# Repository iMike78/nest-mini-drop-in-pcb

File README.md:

<div align="right">
  <details>
    <summary >🌐 Language</summary>
    <div>
      <div align="center">
        <a href="https://openaitx.github.io/view.html?user=iMike78&project=nest-mini-drop-in-pcb&lang=en">English</a>
        | <a href="https://openaitx.github.io/view.html?user=iMike78&project=nest-mini-drop-in-pcb&lang=zh-CN">简体中文</a>
        | <a href="https://openaitx.github.io/view.html?user=iMike78&project=nest-mini-drop-in-pcb&lang=zh-TW">繁體中文</a>
        | <a href="https://openaitx.github.io/view.html?user=iMike78&project=nest-mini-drop-in-pcb&lang=ja">日本語</a>
        | <a href="https://openaitx.github.io/view.html?user=iMike78&project=nest-mini-drop-in-pcb&lang=ko">한국어</a>
        | <a href="https://openaitx.github.io/view.html?user=iMike78&project=nest-mini-drop-in-pcb&lang=hi">हिन्दी</a>
        | <a href="https://openaitx.github.io/view.html?user=iMike78&project=nest-mini-drop-in-pcb&lang=th">ไทย</a>
        | <a href="https://openaitx.github.io/view.html?user=iMike78&project=nest-mini-drop-in-pcb&lang=fr">Français</a>
        | <a href="https://openaitx.github.io/view.html?user=iMike78&project=nest-mini-drop-in-pcb&lang=de">Deutsch</a>
        | <a href="https://openaitx.github.io/view.html?user=iMike78&project=nest-mini-drop-in-pcb&lang=es">Español</a>
        | <a href="https://openaitx.github.io/view.html?user=iMike78&project=nest-mini-drop-in-pcb&lang=it">Italiano</a>
        | <a href="https://openaitx.github.io/view.html?user=iMike78&project=nest-mini-drop-in-pcb&lang=ru">Русский</a>
        | <a href="https://openaitx.github.io/view.html?user=iMike78&project=nest-mini-drop-in-pcb&lang=pt">Português</a>
        | <a href="https://openaitx.github.io/view.html?user=iMike78&project=nest-mini-drop-in-pcb&lang=nl">Nederlands</a>
        | <a href="https://openaitx.github.io/view.html?user=iMike78&project=nest-mini-drop-in-pcb&lang=pl">Polski</a>
        | <a href="https://openaitx.github.io/view.html?user=iMike78&project=nest-mini-drop-in-pcb&lang=ar">العربية</a>
        | <a href="https://openaitx.github.io/view.html?user=iMike78&project=nest-mini-drop-in-pcb&lang=fa">فارسی</a>
        | <a href="https://openaitx.github.io/view.html?user=iMike78&project=nest-mini-drop-in-pcb&lang=tr">Türkçe</a>
        | <a href="https://openaitx.github.io/view.html?user=iMike78&project=nest-mini-drop-in-pcb&lang=vi">Tiếng Việt</a>
        | <a href="https://openaitx.github.io/view.html?user=iMike78&project=nest-mini-drop-in-pcb&lang=id">Bahasa Indonesia</a>
        | <a href="https://openaitx.github.io/view.html?user=iMike78&project=nest-mini-drop-in-pcb&lang=as">অসমীয়া</
      </div>
    </div>
  </details>

</div>

# MiciMike drop-in PCB replacement for Google Nest Mini

[MiciMike Nest Mini](https://github.com/iMike78/nest-mini-drop-in-pcb) is an open-source drop-in PCB replacement for the ["Google Nest Mini" (Google's second-generation smart speaker with a barrel connector charging port)](https://en.wikipedia.org/wiki/Google_Nest_(smart_speakers)). It is built around the ESP32-S3, ESP32-P4 and (optionally) ESP32-C6 and is meant to run open-source firmware, primarily [ESPHome](https://esphome.io).

Tip! If you are instead looking for a similar drop-in PCB replacement for the "Google Home Mini" (Google's first-generation smart speaker with a Micro-USB charging port), check out the sister project at https://github.com/iMike78/home-mini-v1-drop-in-pcb

Both are fully open-source hardware projects. They take concept inspiration from the [Onju Voice](https://github.com/justLV/onju-voice) and from the [Home Assistant Voice Preview Edition](https://www.home-assistant.io/blog/2024/12/19/voice-preview-edition-the-era-of-open-voice/) by the Open Home Foundation and Nabu Casa.

# Project scope

The goal of this project is a custom replacement PCB for the Google Nest Mini (2nd Gen) that fits the original enclosure and reuses the original speaker, power supply, flex cable, mute switch and touch surface.

It primarily targets people who want to convert their old Google Nest Mini into an open-source [voice satellite for Home Assistant](https://www.home-assistant.io/voice_control/) and/or a media-player speaker for [Music Assistant](https://www.music-assistant.io). Because it is based on the Espressif ESP32 platform, the hardware can be used with other firmware as well.

### Relation to the Home Assistant Voice Preview Edition

Earlier revisions of this board followed the Voice Preview Edition (Voice PE) reference design closely, including its XMOS XU316 audio processor. The goal is still the same kind of device: a local, open voice assistant for Home Assistant running ESPHome, with on-device wake word detection and a cleaned-up microphone signal.

The hardware has since moved away from the Voice PE. Microcontroller technology has evolved beyond the XMOS-based approach, and this revision uses an ESP32-P4 for audio processing instead. The P4 may not outperform the XMOS in every respect, but it is a more open platform: it is programmed with Espressif's open-source ESP-IDF, the same ecosystem as the ESP32-S3 and ESPHome, instead of a separate proprietary toolchain. As a result, this board is **not hardware-compatible** with the Voice PE, and the Voice PE firmware does not run on it unchanged.

Developing new ESPHome features is out of scope for this repository. The Voice PE firmware remains a useful reference, and general features belong upstream in ESPHome:

- https://github.com/esphome/home-assistant-voice-pe
  - https://github.com/esphome/esphome
      - https://github.com/esphome/feature-requests

## Current status

> [!CAUTION]
> The rev 3 schematic and PCB are complete and pass ERC/DRC, but the design has **not yet been validated on hardware**. A prototype run is the next step. Do not order production quantities from these files yet.

- Schematic and layout are complete (KiCad 10), with schematic/PCB parity and no unconnected items.
- The final BOM / MPN review is still in progress.
- Mechanical fit of the 5.1 mm tall amplifier output inductors (L11/L12) must be checked on the prototype.
- The ESPHome configuration in this repository (`MiciMike.yaml`) targets an earlier hardware revision and **does not match** the current board.
- ESP32-P4 audio firmware (microphone processing) is under development.

## Hardware variants

One PCB, two assembly variants. They are defined as KiCad 10 design variants, so the BOM, position file and fabrication outputs can be generated per variant.

| Variant | Description | Radios |
|---|---|---|
| **Full** | ESP32-S3 + ESP32-P4 + ESP32-C6 | Wi-Fi 4 / BLE (S3), Wi-Fi 6 / BLE / 802.15.4 Thread & Zigbee (C6) |
| **No C6** | ESP32-S3 + ESP32-P4, the whole ESP32-C6 section not populated | Wi-Fi 4 / BLE (S3) |

In the **No C6** variant all 27 parts of the ESP32-C6 sheet are DNP (U8, Y2, AE2, its RF matching network, decoupling, FB2 and the C6 boot/reset parts). FB2 is the only feed of the C6 supply rail, so the whole C6 power domain is unpowered. The S3 GPIOs that connect to the C6 (reset, GPIO9/boot, UART) must not be used by the firmware in this variant.

Example exports with `kicad-cli`:

```
kicad-cli sch export bom --variant "No C6" -o bom_noC6.csv nest-mini-v2-drop-in-pcb.kicad_sch
kicad-cli pcb export pos --variant "No C6" --exclude-dnp -o pos_noC6.csv nest-mini-v2-drop-in-pcb.kicad_pcb
```

## Architecture

| Block | Part | Role |
|---|---|---|
| Main MCU | ESP32-S3R8 (8 MB PSRAM) + 16 MB W25Q128 flash | Wi-Fi/BLE, ESPHome, wake word, I²S master to the amplifier, I²C master, LEDs, mute detection, boot/reset and UART control of the P4 and C6 |
| Audio processor | ESP32-P4 + 16 MB W25Q128 flash | Microphone input and audio processing (noise suppression, AEC, AGC; firmware in development) |
| Thread / Zigbee (optional) | ESP32-C6FH8 (8 MB in-package flash) | 802.15.4 radio, e.g. OpenThread Border Router (ESP-IDF `ot_br`) |
| Amplifier | TAS5805M (TAS5805MPWPR) | Class-D amplifier with DSP, I²S audio, I²C control by the S3 |
| Microphones | 3x TDK InvenSense T3902 (MMICT390200012) | PDM MEMS microphones to the ESP32-P4 |
| Touch | MPR121 | Capacitive touch on the original touch surface, I²C with IRQ to the S3 |
| LEDs | 4x SK6805-EC20 + 2x SK6812D-EC3210R (side-emitting, board edge) | Addressable RGB, driven by the S3 through an SN74AHCT1G125 3.3 V to 5 V level shifter |

The ESP32-P4 replaces the XMOS XU316 used in earlier revisions.

### Inter-chip links

- **S3 → amplifier:** I²S (BCLK, LRCK, SDIN) and I²C control.
- **Amplifier → P4 (AEC reference):** the TAS5805M SDOUT goes to the ESP32-P4, which receives BCLK/LRCK from the same I²S bus, so the P4 gets the post-DSP playback signal as the echo-cancellation reference.
- **S3 ↔ P4:** I²S data line from the P4 to the S3 (I2S_DIN_SEC, processed microphone audio) and a second I²S clock pair (I2S2 BCLK/LRCLK), plus UART, P4_BOOT and P4_RST driven by the S3.
- **S3 ↔ C6:** UART plus C6 reset and GPIO9 (boot), driven by the S3, for firmware updates of the C6 from the S3.
- **I²C bus:** S3, TAS5805M and MPR121.

## Power

- **Input:** 14 V from the original Nest Mini power supply (14 V / 1.1 A), through the original flex cable (Hirose FH34SRJ-10S, 14 V on pins 7–10).
- **Protection:** PMEG4030ER Schottky diode in series (reverse polarity) and SMAJ15A TVS on the 14 V rail.
- **Rails:**
  - 14 V → TPS62130 → 5 V (LEDs, microphone LDO, LED level shifter)
  - 5 V → TPS62130 → 3.3 V, then separate filtered branches through ferrite beads for the S3, P4 and C6
  - 3.3 V → TLV62569 → ESP32-P4 core supply (ESP_VDD_HP)
  - 14 V → TAS5805M PVDD
  - 5 V → TLV73333 → microphone supply (switched off by the mute switch)
- **Bench supply / test pads:**

| Pad | Rail | Type | Powers |
|---|---|---|---|
| TP1 (+) / TP4 (GND) | +14 V, **max 15 V** | 3 mm THT pads (front) | the whole board, including the amplifier |
| TP2 | +5 V | 1 mm test pad (back) | everything except the amplifier (TAS5805M PVDD stays off) |
| TP3 | +3.3 V | 1 mm test pad (back) | the ESP32s, flash, touch controller; no LEDs, no microphones, no amplifier |

Use only one supply input at a time. When feeding +5 V or +3.3 V directly, the rail above it is not driven, and the regulator in front of it may be back-powered through its internal switch.

> ⚠️ There is no USB-C port on this revision. The board is powered through the original flex cable or the bench / test pads above.

## Audio

- TAS5805M in **mono PBTL** mode with pre-filter paralleling (OUT_A+ ∥ OUT_A− → L11 and OUT_B+ ∥ OUT_B− → L12, per TI TAS5805M PBTL wiring), output filter with 2x Coilcraft XAL5050-103 (10 µH) inductors.
- Original 4 Ω / 15 W speaker. The original firmware limits the amplifier to about 40 %. The firmware must set PBTL mode (`DAMP_PBTL`) and a gain / power limit that suits the speaker and the 14 V / 1.1 A supply.
- Speaker connection: TE 1775443-2 connector (J5) or the parallel solder pads TP8/TP9.

## Microphones and mute

- 3 PDM microphones, connected to the ESP32-P4 through an SN74LVC125A buffer.
- The original mute slide switch (flex cable pin 2) is read by the S3 and also acts **in hardware**: in the muted position the microphone LDO is switched off and the buffer outputs go high-impedance, so the microphones cannot be enabled from firmware.

## Programming

Each ESP has its own unpopulated 5-pin pogo / header footprint: GND, BOOT, RST, USB D−, USB D+.

| Header | Chip | USB |
|---|---|---|
| J1 | ESP32-S3 | native USB (USB Serial/JTAG) |
| J2 | ESP32-C6 | native USB (USB Serial/JTAG) |
| J3 | ESP32-P4 | USB 1.1 FS (GPIO24/25) |

After the first flash, the S3 can update the P4 and the C6 over UART, controlling their boot and reset lines.

## PCB

- 4 layers, 1.6 mm: F.Cu signal / In1 solid GND / In2 power planes / B.Cu signal.
- All vias 0.4 / 0.3 mm (24 thermal vias under the TAS5805M).
- Two Johanson 2450AT18A100E chip antennas (S3 and C6), each with its own keepout, LC matching network, RF netclass and GND via fence.
- GND stitching vias along the board edge.
- Custom DRC rules (`.kicad_dru`) allow the narrow RF track at the ESP32-S3 and ESP32-C6 antenna pins.
- Intentional DRC exclusions (microphone pads at the acoustic openings, touch pads with NPTH, I²S fan-out, programming footprint overlap) are documented with reasons in the project file.

## Hardware changes compared to rev 2

- XMOS XU316 replaced by ESP32-P4 (with its own flash and TLV62569 core supply).
- ESP32-C6 section added as an assembly option (Full / No C6 variants).
- USB-C input, FUSB302B PD controller, USB mux and the GPIO expander removed. Power comes from the original 14 V input, or from the 14 V / 5 V / 3.3 V bench and test pads.
- Programming moved to per-chip pogo footprints with USB.
- S3 controls the P4 and C6 boot/reset lines and has a UART to both.
- 14 V input protection added (series Schottky + TVS), plus bench supply pads TP1/TP4 (14 V) and test pads TP2 (5 V) / TP3 (3.3 V).
- Speaker solder pads TP8/TP9 added next to the speaker connector.
- TAS5805M changed to mono PBTL with 10 µH / XAL5050 output inductors.
- Microphone buffer and microphone LDO controlled by the hardware mute switch.
- TPS62130 regulators: DEF tied to GND, PG not used.
- Complete re-layout in KiCad 10, with RF keepouts, matching networks and via fencing for both antennas.

## Tools used

- 🛠️ KiCad 10
- 🧰 SnapEDA / LCSC for footprint sourcing

## References

### Home Assistant Voice Preview Edition resources (inspiration)
- https://www.home-assistant.io/blog/2024/12/19/voice-preview-edition-the-era-of-open-voice/
  - https://voice-pe.home-assistant.io/resources/
    - https://support.nabucasa.com/hc/en-us/articles/26195279589277-Home-Assistant-Voice-Preview-Edition-PCB-design-files
      - https://raw.githubusercontent.com/NabuCasa/support/refs/heads/main/static/docs/voice/home_assistant_voice_pe_schematic_v1.0_241009.pdf

#### ESPHome firmware for Home Assistant Voice PE

- https://github.com/esphome/home-assistant-voice-pe
  - https://esphome.github.io/home-assistant-voice-pe/
- https://voice-pe.home-assistant.io/

### ESP32-P4 resources

- https://www.espressif.com/en/products/socs/esp32-p4
- https://documentation.espressif.com/esp32-p4_datasheet_en.html
- https://docs.espressif.com/projects/esp-idf/en/latest/esp32p4/

## License

This project is licensed under the [CERN Open Hardware License Version 2 - Strongly Reciprocal (CERN-OHL-S v2)](LICENCE).
Any modified version of this hardware must also be distributed under the same license.

## Development note

AI agents were used as assistants during the development of this hardware, for design review, verification and documentation. All design decisions and the final design files are the author's own.

☕ If you'd like to support this project, feel free to [buy me a coffee on Ko-fi](https://ko-fi.com/imike78)!

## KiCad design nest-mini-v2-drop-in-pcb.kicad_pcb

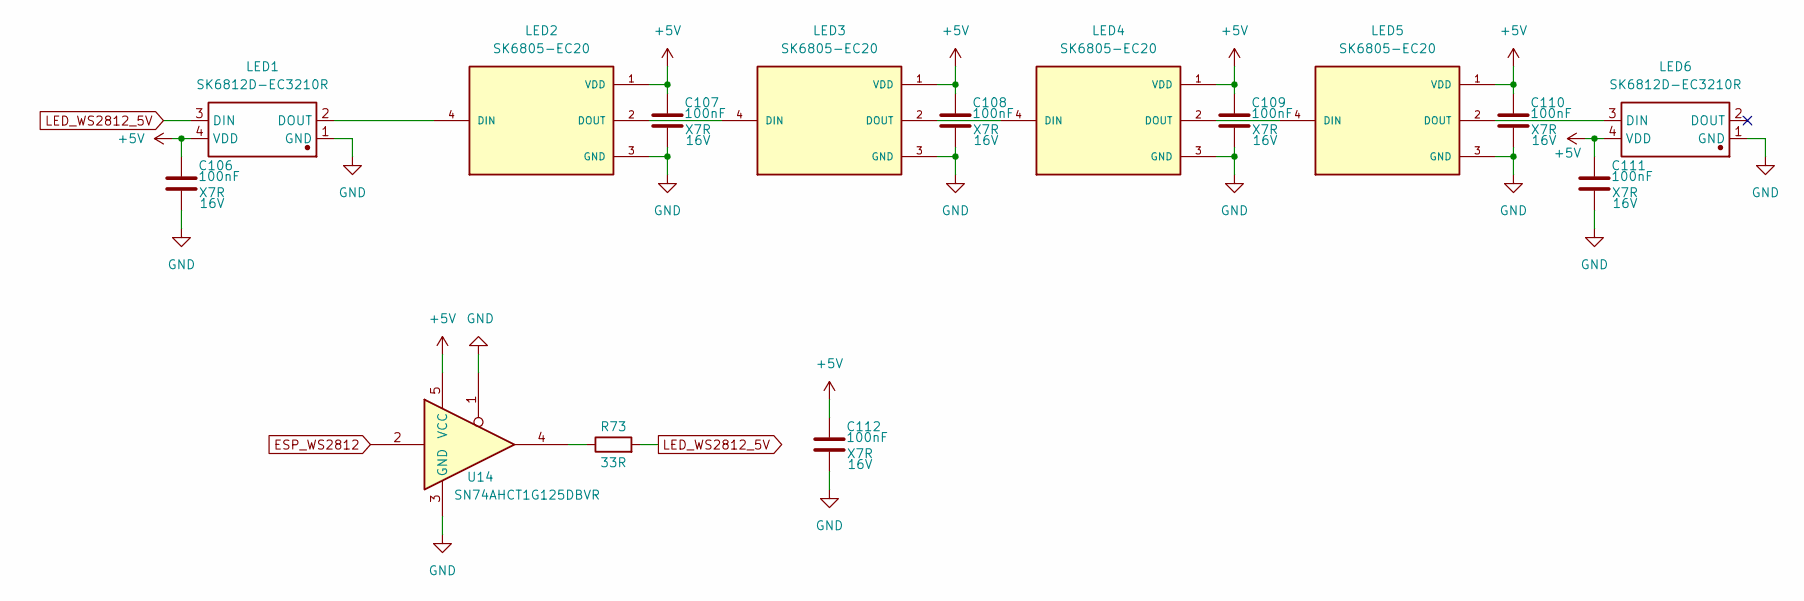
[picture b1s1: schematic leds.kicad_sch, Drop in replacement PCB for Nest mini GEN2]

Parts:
C106, C107, C108, C109, C110, C111, C112: 100nF; C_0402_1005Metric; Voltage 16V; Manufacturer Part CL05B104KO5NNNC; LCSC Part # C1525
LED1, LED6: SK6812D-EC3210R; LED-SMD_4P_SK6812D-EC3210R; Manufacturer Part SK6812D-EC3210R; LCSC Part # C2890041
LED2, LED3, LED4, LED5: SK6805-EC20; Manufacturer Part SK6805-EC20; LCSC Part # C2890036
R73: 33R; R_0402_1005Metric; Tolerance 1%; Manufacturer Part 0402WGF330JTCE; LCSC Part # C25105
U14: SN74AHCT1G125DBVR; SOT-23-5; Manufacturer Part SN74AHCT1G125DBVR; LCSC Part # C7484

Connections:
+5V: C106.1, C107.1, C108.1, C109.1, C110.1, C111.1, C112.1, LED1.4 (VDD), LED2.1 (VDD), LED3.1 (VDD), LED4.1 (VDD), LED5.1 (VDD), LED6.4 (VDD), U14.5 (VCC); also elsewhere on the board
ESP_WS2812: U14.2; also elsewhere on the board
GND: C106.2, C107.2, C108.2, C109.2, C110.2, C111.2, C112.2, LED1.1 (GND), LED2.3 (GND), LED3.3 (GND), LED4.3 (GND), LED5.3 (GND), LED6.1 (GND), U14.1, U14.3 (GND); also elsewhere on the board
LED_WS2812_5V: LED1.3 (DIN), R73.2
unnamed: LED1.2 (DOUT), LED2.4 (DIN)
unnamed: LED2.2 (DOUT), LED3.4 (DIN)
unnamed: LED3.2 (DOUT), LED4.4 (DIN)
unnamed: LED4.2 (DOUT), LED5.4 (DIN)
unnamed: LED5.2 (DOUT), LED6.3 (DIN)
unnamed: R73.1, U14.4

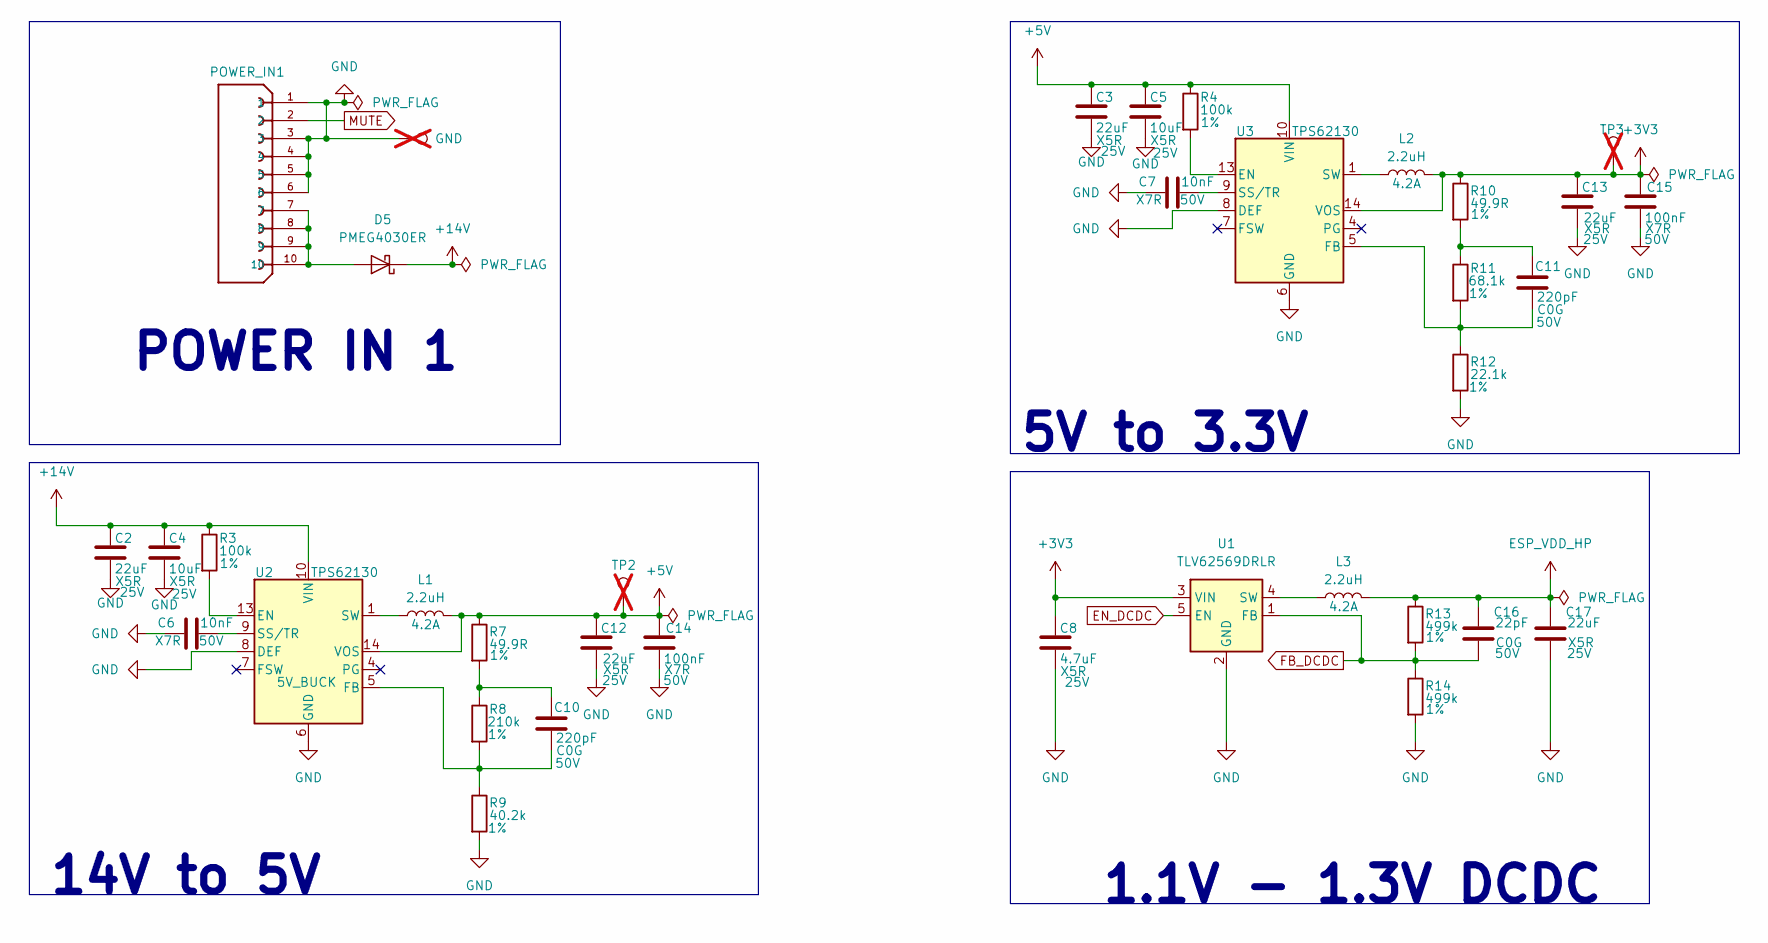
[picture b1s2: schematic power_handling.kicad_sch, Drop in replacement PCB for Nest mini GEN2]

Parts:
C2, C3, C12, C13, C17: 22uF; C_0805_2012Metric; Voltage 25V; Manufacturer Part CL21A226MAQNNNE; LCSC Part # C45783
C4, C5: 10uF; C_0805_2012Metric; Voltage 25V; Manufacturer Part CL21A106KAYNNNE; LCSC Part # C15850
C6, C7: 10nF; C_0402_1005Metric; Voltage 50V; Manufacturer Part CL05B103KB5NNNC; LCSC Part # C15195
C8: 4.7uF; C_0805_2012Metric; Voltage 25V; Manufacturer Part CL21A475KAQNNNE; LCSC Part # C1779
C10, C11: 220pF; C_0603_1608Metric; Voltage 50V; Manufacturer Part 0603CG221J500NT; LCSC Part # C156398
C14, C15: 100nF; C_0805_2012Metric; Voltage 50V; Manufacturer Part CC0805KRX7R9BB104; LCSC Part # C49678
C16: 22pF; C_0402_1005Metric; Voltage 50V; Manufacturer Part 0402CG220J500NT; LCSC Part # C1555
D5: PMEG4030ER; Nexperia_CFP3_SOD-123W; Manufacturer Part PMEG4030ER,115; LCSC Part # C389355
L1, L2, L3: 2.2uH; IND_SRP4020TA-2R2M; Manufacturer Part SRP4020TA-2R2M; LCSC Part # C719179
POWER_IN1: FH34SRJ-10S-0.5SH_50_; HRS_FH34SRJ-10S-0.5SH_50_; Manufacturer Part FH34SRJ-10S-0.5SH(50); LCSC Part # C324723
R3, R4: 100k; R_0402_1005Metric; Tolerance 1%; Manufacturer Part 0402WGF1003TCE; LCSC Part # C25741
R7, R10: 49.9R; R_0603_1608Metric; Tolerance 1%; Manufacturer Part 0603WAF499JT5E; LCSC Part # C23185
R8: 210k; R_0603_1608Metric; Tolerance 1%; Manufacturer Part 0603WAF2103T5E; LCSC Part # C22952
R9: 40.2k; R_0603_1608Metric; Tolerance 1%; Manufacturer Part 0603WAF4022T5E; LCSC Part # C12447
R11: 68.1k; R_0603_1608Metric; Tolerance 1%; Manufacturer Part 0603WAF6812T5E; LCSC Part # C25976
R12: 22.1k; R_0603_1608Metric; Tolerance 1%; Manufacturer Part 0603WAF2212T5E; LCSC Part # C25961
R13, R14: 499k; R_0603_1608Metric; Tolerance 1%; Manufacturer Part ARG03DTC4993; LCSC Part # C2828669
TP2: +5V; TestPoint_Pad_D1.0mm; not fitted
TP3: +3V3; TestPoint_Pad_D1.0mm; not fitted
TP4: GND; TestPoint_THTPad_D3.0mm_Drill1.5mm; not fitted
U1: TLV62569DRLR; SOT-563; Manufacturer Part TLV62569DRLR
U2, U3: TPS62130; VQFN-16-1EP_3x3mm_P0.5mm_EP1.68x1.68mm_ThermalVias; Manufacturer Part TPS62130ARGTR; LCSC Part # C337502

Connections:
+3V3: C8.1, C13.1, C15.1, L2.2, R10.1, TP3.1 (1_1), U1.3 (VIN), U3.14 (VOS); also elsewhere on the board
+5V: C3.1, C5.1, C12.1, C14.1, L1.2, R4.1, R7.1, TP2.1 (1_1), U2.14 (VOS), U3.10 (VIN), U3.11 (VIN), U3.12 (VIN); also elsewhere on the board
+14V: C2.1, C4.1, D5.1 (K), R3.1, U2.10 (VIN), U2.11 (VIN), U2.12 (VIN); also elsewhere on the board
EN_DCDC: U1.5 (EN); also elsewhere on the board
ESP_VDD_HP: C16.1, C17.1, L3.2, R13.1; also elsewhere on the board
FB_DCDC: C16.2, R13.2, R14.1, U1.1 (FB); also elsewhere on the board
GND: C2.2, C3.2, C4.2, C5.2, C6.1, C7.1, C8.2, C12.2, C13.2, C14.2, C15.2, C17.2, POWER_IN1.1, POWER_IN1.3, POWER_IN1.4, POWER_IN1.5, POWER_IN1.6, R9.2, R12.2, R14.2, TP4.1 (1_1), U1.2 (GND), U2.6 (GND), U2.8 (DEF), U2.15 (GND), U2.16 (GND), U2.17 (GND), U3.6 (GND), U3.8 (DEF), U3.15 (GND), U3.16 (GND), U3.17 (GND); also elsewhere on the board
MUTE: POWER_IN1.2; also elsewhere on the board
unnamed: C10.1, R7.2, R8.1
unnamed: C11.1, R10.2, R11.1
unnamed: D5.2 (A), POWER_IN1.7, POWER_IN1.8, POWER_IN1.9, POWER_IN1.10
unnamed: L1.1, U2.1 (SW), U2.2 (SW), U2.3 (SW)
unnamed: L2.1, U3.1 (SW), U3.2 (SW), U3.3 (SW)
unnamed: L3.1, U1.4 (SW)
unnamed: R3.2, U2.13 (EN)
unnamed: C10.2, R8.2, R9.1, U2.5 (FB)
unnamed: C6.2, U2.9 (SS/TR)
unnamed: R4.2, U3.13 (EN)
unnamed: C11.2, R11.2, R12.1, U3.5 (FB)
unnamed: C7.2, U3.9 (SS/TR)

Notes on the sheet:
POWER IN 1
14V to 5V
1.1V - 1.3V DCDC
5V to 3.3V

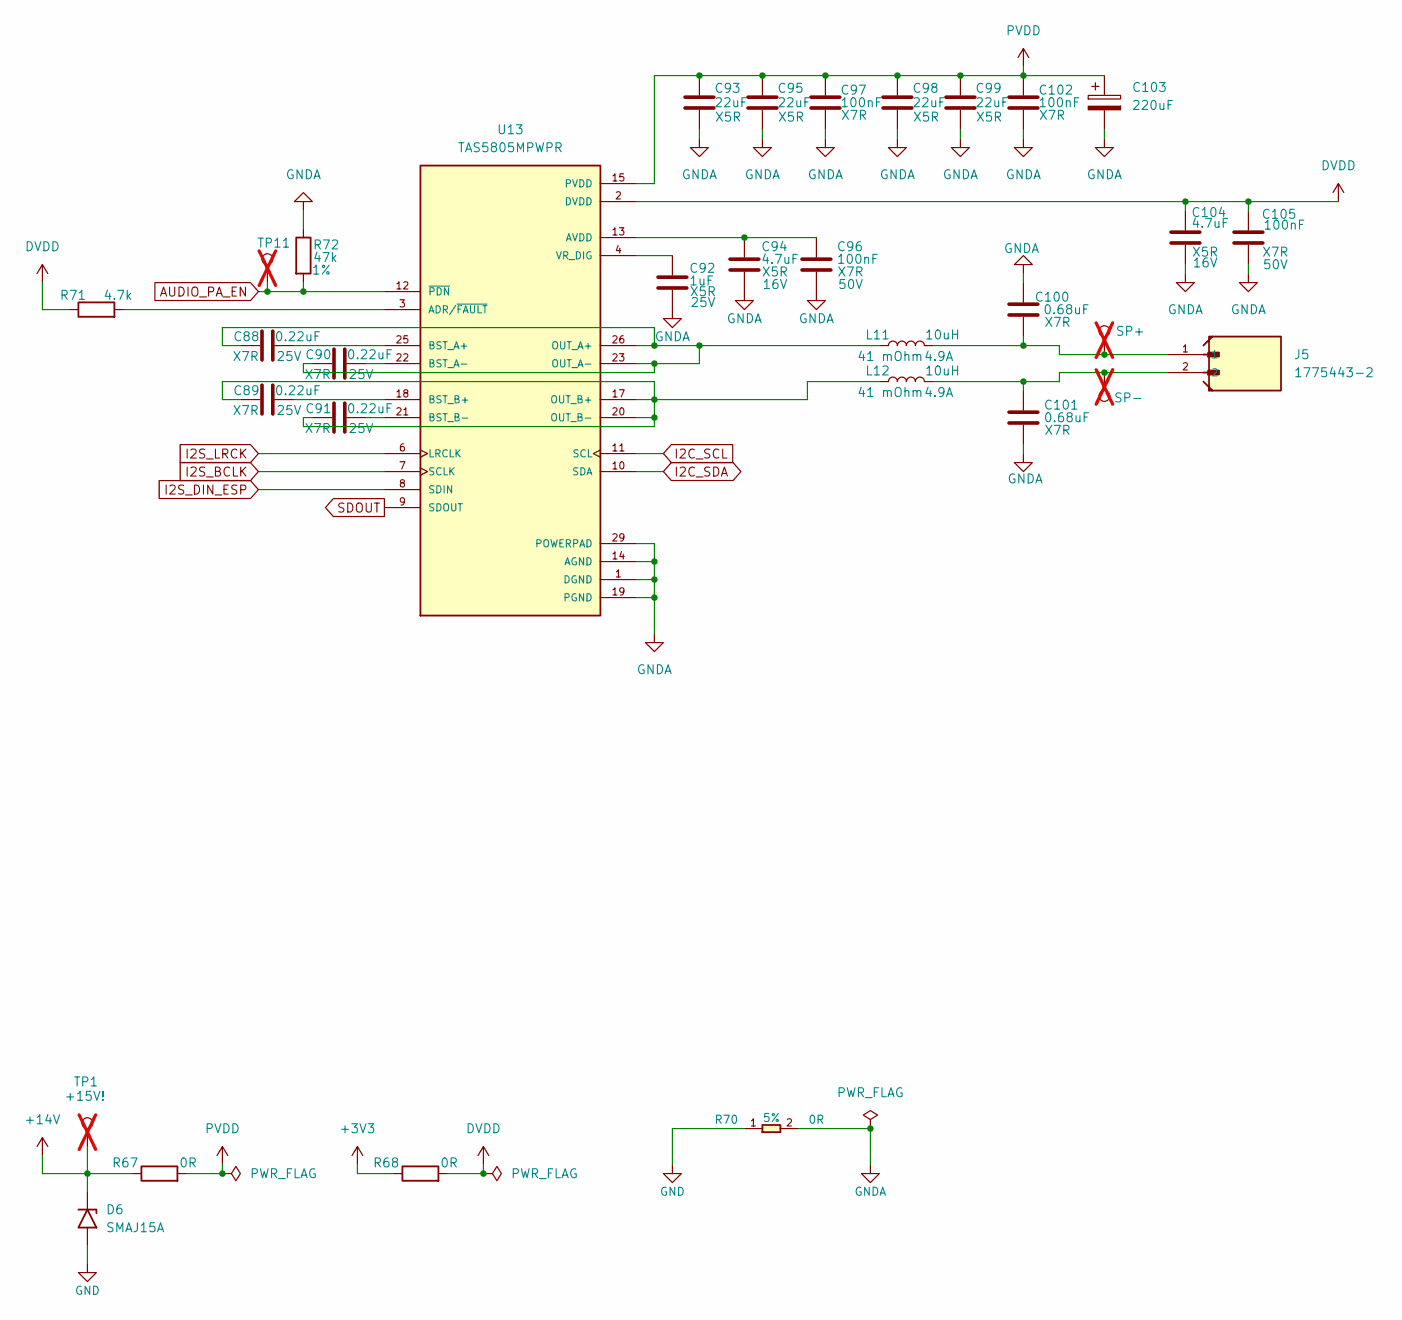
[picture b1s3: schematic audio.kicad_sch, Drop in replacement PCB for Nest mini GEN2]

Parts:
C88, C89, C90, C91: 0.22uF; C_0603_1608Metric; Voltage 25V; Manufacturer Part CL10B224KA8NNNC; LCSC Part # C21120
C92: 1uF; C_0402_1005Metric; Voltage 25V; Manufacturer Part CL05A105KA5NQNC; LCSC Part # C52923
C93, C95, C98, C99: 22uF; C_0805_2012Metric; Voltage 25V; Manufacturer Part CL21A226MAQNNNE; LCSC Part # C45783
C94, C104: 4.7uF; C_0603_1608Metric; Voltage 16V; Manufacturer Part CL10A475KO8NNNC; LCSC Part # C19666
C96, C105: 100nF; C_0603_1608Metric; Voltage 50V; Manufacturer Part CC0603KRX7R9BB104; LCSC Part # C14663
C97, C102: 100nF; C_0402_1005Metric; Voltage 50V; Manufacturer Part CC0402KRX7R9BB104; LCSC Part # C131394
C100, C101: 0.68uF; C_0805_2012Metric; Voltage 50V; Manufacturer Part CL21B684KBFVPNE; LCSC Part # C472832
C103: 220uF; C_Elec_6.3x7.7; Voltage 25V; Manufacturer Part MA25V220M6X8; LCSC Part # C46550464
D6: SMAJ15A; D_SMA; Manufacturer Part SMAJ15A; LCSC Part # C148216
J5: 1775443-2; PARTREV B5; LCSC Part # C5162845
L11, L12: 10uH; L_Coilcraft_XAL5050-XXX; Manufacturer Part XAL5050-103MEC; LCSC Part # C5441578
R67: 0R; R_1206_3216Metric; Manufacturer Part 1206W4F0000T5E; LCSC Part # C17888
R68: 0R; R_0603_1608Metric; Manufacturer Part 0603WAF0000T5E; LCSC Part # C21189
R70: 0R; R_0805_2012Metric; Tolerance 5%; MPN 0805W8F0000T5E; LCSC Part # C17477
R71: 4.7k; R_0402_1005Metric; Manufacturer Part 0402WGF4701TCE; LCSC Part # C25900
R72: 47k; R_0402_1005Metric; Tolerance 1%; Manufacturer Part 0402WGF4702TCE; LCSC Part # C25792
TP1: +15V!; TestPoint_THTPad_D3.0mm_Drill1.5mm; not fitted
TP8: SP+; TestPoint_Pad_D2.0mm; not fitted
TP9: SP-; TestPoint_Pad_D2.0mm; not fitted
TP11: PA_EN; TestPoint_Pad_D1.0mm; not fitted
U13: TAS5805MPWPR; Manufacturer Part TAS5805MPWPR; LCSC Part # C478472

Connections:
+3V3: R68.1; also elsewhere on the board
+14V: D6.1 (A1), R67.1, TP1.1 (1_1); also elsewhere on the board
AUDIO_PA_EN: R72.2, TP11.1 (1_1), U13.12 (~PDN); also elsewhere on the board
DVDD: C104.1, C105.1, R68.2, R71.1, U13.2 (DVDD)
GND: D6.2 (A2), R70.1; also elsewhere on the board
GNDA: C92.2, C93.2, C94.2, C95.2, C96.2, C97.2, C98.2, C99.2, C100.2, C101.2, C102.2, C103.2, C104.2, C105.2, R70.2, R72.1, U13.1 (DGND), U13.5 (DGND), U13.14 (AGND), U13.19 (PGND), U13.24 (PGND), U13.29 (POWERPAD), U13.30 (POWERPAD), U13.31 (POWERPAD), U13.32 (POWERPAD), U13.33 (POWERPAD), U13.34 (POWERPAD), U13.35 (POWERPAD), U13.36 (POWERPAD), U13.37 (POWERPAD), U13.38 (POWERPAD), U13.39 (POWERPAD), U13.40 (POWERPAD), U13.41 (POWERPAD), U13.42 (POWERPAD), U13.43 (POWERPAD), U13.44 (POWERPAD), U13.45 (POWERPAD), U13.46 (POWERPAD), U13.47 (POWERPAD), U13.48 (POWERPAD), U13.49 (POWERPAD), U13.50 (POWERPAD), U13.51 (POWERPAD), U13.52 (POWERPAD), U13.53 (POWERPAD)
I2C_SCL: U13.11 (SCL); also elsewhere on the board
I2C_SDA: U13.10 (SDA); also elsewhere on the board
I2S_BCLK: U13.7 (SCLK); also elsewhere on the board
I2S_DIN_ESP: U13.8 (SDIN); also elsewhere on the board
I2S_LRCK: U13.6 (LRCLK); also elsewhere on the board
unnamed: C100.1, J5.1, L11.2, TP8.1 (1_1)
unnamed: C101.1, J5.2, L12.2, TP9.1 (1_1)
unnamed: R71.2, U13.3 (ADR/~FAULT)
unnamed: C94.1, C96.1, U13.13 (AVDD)
unnamed: C88.2, U13.25 (BST_A+)
unnamed: C90.2, U13.22 (BST_A-)
unnamed: C89.2, U13.18 (BST_B+)
unnamed: C91.2, U13.21 (BST_B-)
unnamed: C88.1, C90.1, L11.1, U13.23 (OUT_A-), U13.26 (OUT_A+)
unnamed: C89.1, C91.1, L12.1, U13.17 (OUT_B+), U13.20 (OUT_B-)
unnamed: C92.1, U13.4 (VR_DIG)
PVDD: C93.1, C95.1, C97.1, C98.1, C99.1, C102.1, C103.1, R67.2, U13.15 (PVDD), U13.16 (PVDD), U13.27 (PVDD), U13.28 (PVDD)
SDOUT: U13.9 (SDOUT); also elsewhere on the board

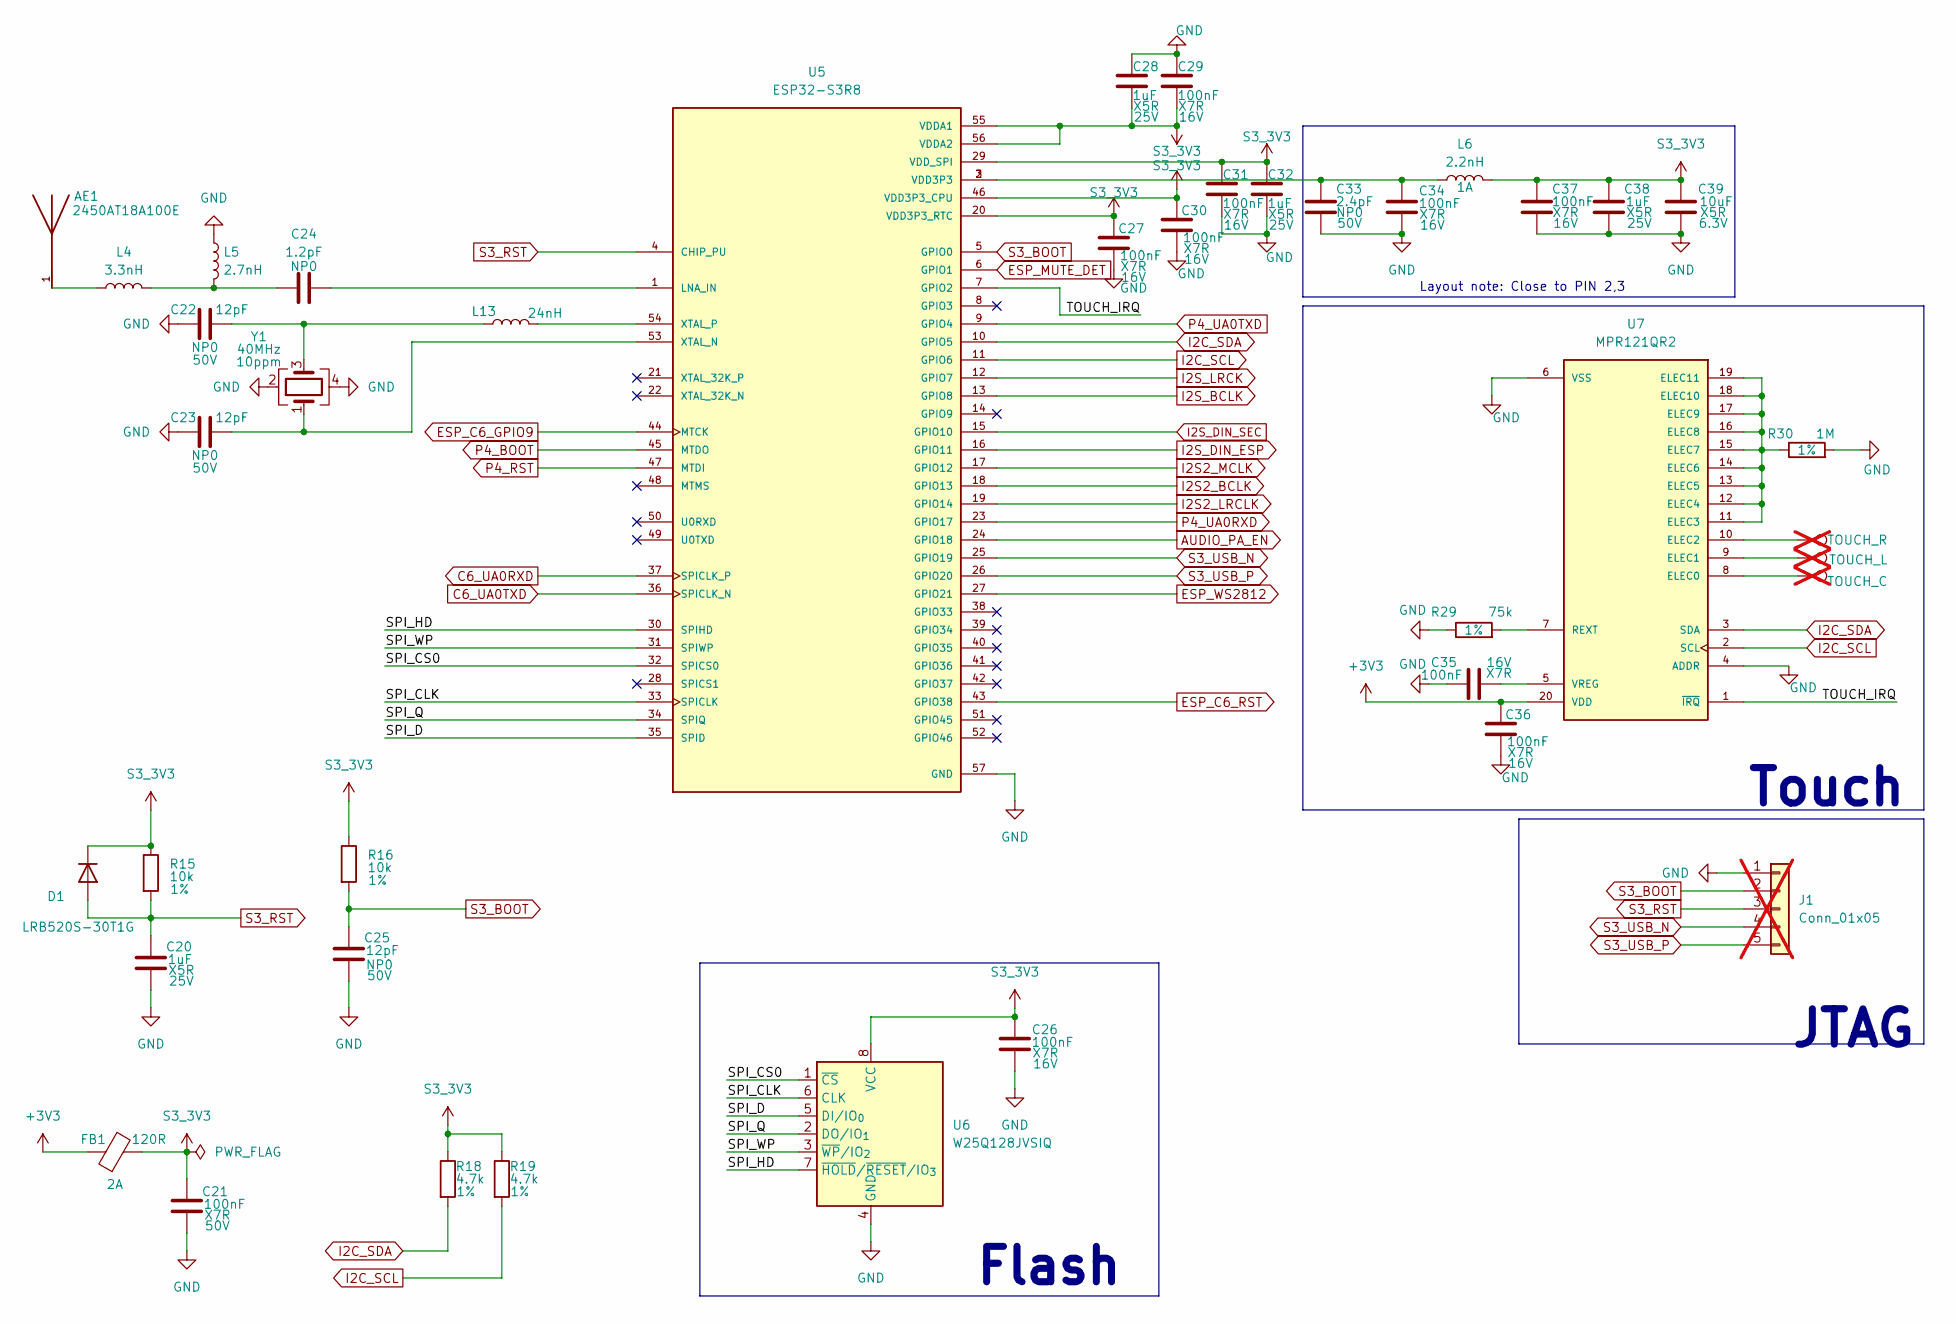
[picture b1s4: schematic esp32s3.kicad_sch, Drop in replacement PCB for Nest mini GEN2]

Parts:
AE1: 2450AT18A100E; Johanson_2450AT18x100; PARTREV 1.3; LCSC Part # C89334
C20, C28, C32, C38: 1uF; C_0402_1005Metric; Voltage 25V; Manufacturer Part CL05A105KA5NQNC; LCSC Part # C52923
C21: 100nF; C_0603_1608Metric; Voltage 50V; Manufacturer Part CC0603KRX7R9BB104; LCSC Part # C14663
C22, C23, C25: 12pF; C_0402_1005Metric; Voltage 50V; Manufacturer Part 0402CG120J500NT; LCSC Part # C1547
C24: 1.2pF; C_0402_1005Metric; Voltage 50V; Manufacturer Part CC0402BRNPO9BN1R2; LCSC Part # C327292
C26, C27, C29, C30, C31, C34, C35, C36, C37: 100nF; C_0402_1005Metric; Voltage 16V; Manufacturer Part CL05B104KO5NNNC; LCSC Part # C1525
C33: 2.4pF; C_0402_1005Metric; Voltage 50V; Manufacturer Part 0402CG2R4C500NT; LCSC Part # C48346
C39: 10uF; C_0402_1005Metric; Voltage 6.3V; Manufacturer Part CL05A106MQ5NUNC; LCSC Part # C15525
D1: LRB520S-30T1G; D_SOD-523; Manufacturer Part LRB520S-30T1G; LCSC Part # C83680
FB1: 120R; BLM18PG121SN1D; Part number BLM18PG121SN1D; LCSC Part # C14709
J1: Conn_01x05; PinHeader_1x05_P2.54mm_Vertical; not fitted
L4: 3.3nH; L_0402_1005Metric; Manufacturer Part SDCL1005C3N3STDF; LCSC Part # C16526
L5: 2.7nH; L_0402_1005Metric; Manufacturer Part MHQ1005P2N7BT000; LCSC Part # C434826
L6: 2.2nH; L_0402_1005Metric; Manufacturer Part LQG15HS2N2B02D; LCSC Part # C162540
L13: 24nH; L_0402_1005Metric; Manufacturer Part LQW15AN24NJ00D; LCSC Part # C341784
R15, R16: 10k; R_0402_1005Metric; Tolerance 1%; Manufacturer Part 0402WGF1002TCE; LCSC Part # C25744
R18, R19: 4.7k; R_0402_1005Metric; Tolerance 1%; Manufacturer Part 0402WGF4701TCE; LCSC Part # C25900
R29: 75k; R_0402_1005Metric; Tolerance 1%; Manufacturer Part FRC0402F7502TS; LCSC Part # C2909383
R30: 1M; R_0402_1005Metric; Tolerance 1%; Manufacturer Part 0402WGF1004TCE; LCSC Part # C26083
TP5: TOUCH_R; Touchpad; not fitted
TP6: TOUCH_C; Touchpad; not fitted
TP7: TOUCH_L; Touchpad; not fitted
U5: ESP32-S3R8; QFN40P700X700X90-57N; Manufacturer Part ESP32-S3R8; LCSC Part # C2913194
U6: W25Q128JVSIQ; SOIC-8_5.3x5.3mm_P1.27mm; Manufacturer Part W25Q128JVSIQ; LCSC Part # C97521
U7: MPR121QR2; MPN MPR121QR2; LCSC Part # C91322
Y1: 40MHz; Crystal_SMD_2016-4Pin_2.0x1.6mm; Tolerance 10ppm; Manufacturer Part XRCGB40M000F1S1BR0; LCSC Part # C1870451

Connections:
+3V3: C36.1, FB1.1, U7.20 (VDD); also elsewhere on the board
/ESP32-S3R8/SPI_CLK: U5.33 (SPICLK), U6.6 (CLK)
/ESP32-S3R8/SPI_CS0: U5.32 (SPICS0), U6.1 (~CS)
/ESP32-S3R8/SPI_D: U5.35 (SPID), U6.5 (DI/IO_{0})
/ESP32-S3R8/SPI_HD: U5.30 (SPIHD), U6.7 (~HOLD/~RESET/IO_{3})
/ESP32-S3R8/SPI_Q: U5.34 (SPIQ), U6.2 (DO/IO_{1})
/ESP32-S3R8/SPI_WP: U5.31 (SPIWP), U6.3 (~WP/IO_{2})
/ESP32-S3R8/TOUCH_IRQ: U5.7 (GPIO2), U7.1 (~IRQ)
AUDIO_PA_EN: U5.24 (GPIO18); also elsewhere on the board
C6_UA0RXD: U5.37 (SPICLK_P); also elsewhere on the board
C6_UA0TXD: U5.36 (SPICLK_N); also elsewhere on the board
ESP_C6_GPIO9: U5.44 (MTCK); also elsewhere on the board
ESP_C6_RST: U5.43 (GPIO38); also elsewhere on the board
ESP_MUTE_DET: U5.6 (GPIO1); also elsewhere on the board
ESP_WS2812: U5.27 (GPIO21); also elsewhere on the board
GND: C20.2, C21.2, C22.1, C23.1, C25.2, C26.2, C27.2, C28.1, C29.1, C30.2, C31.2, C32.2, C33.2, C34.2, C35.1, C36.2, C37.2, C38.2, C39.2, J1.1, L5.1, R29.1, R30.2, U5.57 (GND), U6.4 (GND), U7.4 (ADDR), U7.6 (VSS), Y1.2, Y1.4; also elsewhere on the board
I2C_SCL: R19.2, U5.11 (GPIO6), U7.2 (SCL); also elsewhere on the board
I2C_SDA: R18.2, U5.10 (GPIO5), U7.3 (SDA); also elsewhere on the board
I2S2_BCLK: U5.18 (GPIO13); also elsewhere on the board
I2S2_LRCLK: U5.19 (GPIO14); also elsewhere on the board
I2S2_MCLK: U5.17 (GPIO12); also elsewhere on the board
I2S_BCLK: U5.13 (GPIO8); also elsewhere on the board
I2S_DIN_ESP: U5.16 (GPIO11); also elsewhere on the board
I2S_DIN_SEC: U5.15 (GPIO10); also elsewhere on the board
I2S_LRCK: U5.12 (GPIO7); also elsewhere on the board
unnamed: AE1.1, L4.1
unnamed: C22.2, L13.1, Y1.3
unnamed: C24.1, L4.2, L5.2
unnamed: C33.1, C34.1, L6.1, U5.2 (VDD3P3), U5.3 (VDD3P3)
unnamed: C24.2, U5.1 (LNA_IN)
unnamed: C23.2, U5.53 (XTAL_N), Y1.1
unnamed: L13.2, U5.54 (XTAL_P)
unnamed: TP6.1 (1_1), U7.8 (ELEC0)
unnamed: TP7.1 (1_1), U7.9 (ELEC1)
unnamed: TP5.1 (1_1), U7.10 (ELEC2)
unnamed: R30.1, U7.11 (ELEC3), U7.12 (ELEC4), U7.13 (ELEC5), U7.14 (ELEC6), U7.15 (ELEC7), U7.16 (ELEC8), U7.17 (ELEC9), U7.18 (ELEC10), U7.19 (ELEC11)
unnamed: R29.2, U7.7 (REXT)
unnamed: C35.2, U7.5 (VREG)
P4_BOOT: U5.45 (MTDO); also elsewhere on the board
P4_RST: U5.47 (MTDI); also elsewhere on the board
P4_UA0RXD: U5.23 (GPIO17); also elsewhere on the board
P4_UA0TXD: U5.9 (GPIO4); also elsewhere on the board
S3_3V3: C21.1, C26.1, C27.1, C28.2, C29.2, C30.1, C31.1, C32.1, C37.1, C38.1, C39.1, D1.1 (K), FB1.2, L6.2, R15.1, R16.1, R18.1, R19.1, U5.20 (VDD3P3_RTC), U5.29 (VDD_SPI), U5.46 (VDD3P3_CPU), U5.55 (VDDA1), U5.56 (VDDA2), U6.8 (VCC); also elsewhere on the board
S3_BOOT: C25.1, J1.2, R16.2, U5.5 (GPIO0)
S3_RST: C20.1, D1.2 (A), J1.3, R15.2, U5.4 (CHIP_PU)
S3_USB_N: J1.4, U5.25 (GPIO19)
S3_USB_P: J1.5, U5.26 (GPIO20)

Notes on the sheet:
Touch
Layout note: Close to PIN 2,3
JTAG
Flash

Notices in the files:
nest-mini-v2-drop-in-pcb.kicad_pcb:
CERN-OHL-S-2.0
